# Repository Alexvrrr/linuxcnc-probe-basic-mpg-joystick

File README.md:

# Кастомный USB-пульт (MPG + аналоговый стик) для LinuxCNC 2.9.10 и Probe Basic

Готовый проект аппаратно-программного пульта ручного управления (Pendant / MPG) для станка с ЧПУ под управлением **LinuxCNC 2.9.10** (плата **Mesa 7i92**) и графического интерфейса **Probe Basic (QtPyVCP)**.

---

## 1. Возможности и архитектура

* **Контроллер пульта:** Arduino Leonardo / Pro Micro (ATmega32U4), работающий как стандартный USB HID-геймпад (`Joystick.h`).
* **Квадратурный MPG-энкодер:** Считывание фаз `A` и `B` по аппаратным прерываниям Arduino (`INT1` / `INT0`), буферизация и мгновенный сброс хвоста очереди при остановке вращения (исключает инерционный «доезд» осей).
* **Выбор активной оси (`X`, `Y`, `Z`):** Перемещение по шагам выполняется при удержании кнопки нужной оси и вращении энкодера (на время удержания аналоговый стик программно блокируется в центр).
* **Переключение шага (`Step`):** Циклический перебор `1.0` → `0.1` → `0.01` мм одной кнопкой с выводом текущего значения на LCD-индикатор в интерфейсе Probe Basic.
* **Непрерывные перемещения:**
  * 2-осевой аналоговый стик (`X`, `Y`) с мёртвой зоной и экспоненциальной кривой отклика (`joyhandle`).
  * Кнопки `Z+` и `Z-` для плавного перемещения по оси Z.
  * Регулировка скорости непрерывных перемещений штатным слайдером **Feed Override** в Probe Basic.
* **Работа в любых режимах:** Поддержка перемещений как до поиска домов (**Joint mode**, `joint.0..2`), так и после (**World mode**, `axis.x/y/z`).
* **Аварийный стоп:** Выделенная аппаратная кнопка `E-Stop`.

---

## 2. Схема распайки пинов Arduino (Leonardo / Pro Micro)

Все дискретные входы (кнопки и фазы энкодера) используют внутреннюю подтяжку к плюсу питания (`INPUT_PULLUP`) и замыкаются на общий провод (**GND**).

| Пин Arduino | Назначение в пульте | Тип сигнала / подключение | Кнопка / Ось в `Joystick.h` | Имя пина в LinuxCNC (`hal_input`) |
| :--- | :--- | :--- | :--- | :--- |
| **D2** (`INT1`) | Энкодер MPG — **Фаза A** | Аппаратное прерывание, замыкание на `GND` | Виртуальная кнопка `7` (`MPG+`) | `input.0.btn-tr` |
| **D3** (`INT0`) | Энкодер MPG — **Фаза B** | Аппаратное прерывание, замыкание на `GND` | Виртуальная кнопка `8` (`MPG-`) | `input.0.btn-tl2` |
| **D4** | Выбор оси **X** (`BTN_X`) | Кнопка без фиксации на `GND` | Кнопка `4` | `input.0.btn-y` |
| **D5** | Выбор оси **Y** (`BTN_Y`) | Кнопка без фиксации на `GND` | Кнопка `5` | `input.0.btn-z` |
| **D6** | Выбор оси **Z** (`BTN_Z`) | Кнопка без фиксации на `GND` | Кнопка `6` | `input.0.btn-tl` |
| **D7** | Непрерывный ход **Z+** (`BTN_ZP`) | Кнопка без фиксации на `GND` | Кнопка `2` | `input.0.btn-a` |
| **D8** | Аварийный стоп **E-Stop** (`BTN_ESTOP`) | Кнопка на `GND` | Кнопка `1` | `input.0.btn-b` |
| **D9** | Переключение шага **Step** (`BTN_STEP`) | Кнопка без фиксации на `GND` | Кнопка `0` | `input.0.btn-c` |
| **D14** (`MISO`) | Непрерывный ход **Z-** (`BTN_ZM`) | Кнопка без фиксации на `GND` | Кнопка `3` | `input.0.btn-x` |
| **A0** | Аналоговый стик — **Ось X** | Средний вывод потенциометра (`0..5V`) | Ось `X` (`0..1023`, инверсия в скетче) | `input.0.abs-x-position` |
| **A1** | Аналоговый стик — **Ось Y** | Средний вывод потенциометра (`0..5V`) | Ось `Y` (`0..1023`, инверсия в HAL) | `input.0.abs-y-position` |
| **VCC / 5V** | Питание периферии | Питание активного MPG и потенциометров стика | — | — |
| **GND** | Общий провод | Общая земля для всех кнопок, стика и MPG | — | — |

> **Примечания по электрической части:**
> * На плате **Arduino Pro Micro** пин `14` подписан как **`MISO`** (верхний правый угол платы).
> * При длине кабеля более 1.5–2 м используйте экранированный кабель (экран на `GND` со стороны Arduino) и керамические конденсаторы `0.1 мкФ` между `A0`/`A1` и `GND`.

---

## 3. Прошивка Arduino (`MPG_Joystick.ino`)

Для компиляции требуется библиотека [ArduinoJoystickLibrary](https://github.com/MHeironimus/ArduinoJoystickLibrary).

```cpp
#include <Joystick.h>

Joystick_ Joystick(
  JOYSTICK_DEFAULT_REPORT_ID,
  JOYSTICK_TYPE_GAMEPAD,
  9, 0,                  // 9 кнопок (индексы 0..8), 0 хатов
  true, true, false,     // Оси X и Y включены, Z выключена
  false, false, false,
  false, false, false,
  false, false
);

// --- Пины подключения ---
const int PIN_ENC_A  = 2;  // Фаза A энкодера (аппаратное прерывание INT1)
const int PIN_ENC_B  = 3;  // Фаза B энкодера (аппаратное прерывание INT0)
const int BTN_X      = 4;  // Выбор оси X
const int BTN_Y      = 5;  // Выбор оси Y
const int BTN_Z      = 6;  // Выбор оси Z
const int BTN_ZP     = 7;  // Непрерывное движение Z+
const int BTN_ZM     = 14; // Непрерывное движение Z-
const int BTN_STEP   = 9;  // Переключение шага (1 -> 0.1 -> 0.01)
const int BTN_ESTOP  = 8;  // Аварийный стоп (E-Stop)
const int ADC_X      = A0; // Аналоговый стик X
const int ADC_Y      = A1; // Аналоговый стик Y

// --- Виртуальные кнопки джойстика для импульсов MPG ---
const int BTN_MPG_PLUS  = 7; // В LinuxCNC: input.0.btn-tr (вращение +)
const int BTN_MPG_MINUS = 8; // В LinuxCNC: input.0.btn-tl2 (вращение -)

// --- Переменные квадратурного энкодера ---
volatile long encTicks = 0;
volatile uint8_t prevAB = 0;

const int8_t QUAD_TABLE[16] = {
   0, -1,  1,  0,
   1,  0,  0, -1,
  -1,  0,  0,  1,
   0,  1, -1,  0
};

const int TICKS_PER_DETENT = 4;

// --- Переменные формирования импульсов и мгновенной остановки ---
long sentDetents = 0;
long prevTicks = 0;
unsigned long lastTickTime = 0;
unsigned long pulseTimer = 0;

int pulseState = 0;
int activeMpgBtn = -1;

const unsigned long PULSE_MS = 2;         // 2 мс импульс + 2 мс пауза (до 250 щелчков/сек)
const unsigned long STOP_TIMEOUT_MS = 25; // Сброс хвоста очереди через 25 мс после остановки руки

// --- Антидребезг кнопок выбора оси ---
bool btnAxisState[3] = {false, false, false};
bool btnAxisLastRaw[3] = {false, false, false};
unsigned long btnAxisTimer[3] = {0, 0, 0};
const unsigned long DEBOUNCE_MS = 20;

void isrEncoder() {
  uint8_t curAB = (digitalRead(PIN_ENC_A) << 1) | digitalRead(PIN_ENC_B);
  uint8_t idx = (prevAB << 2) | curAB;
  encTicks += QUAD_TABLE[idx];
  prevAB = curAB;
}

bool readDebounced(int pin, int idx) {
  bool raw = !digitalRead(pin);
  if (raw != btnAxisLastRaw[idx]) {
    btnAxisTimer[idx] = millis();
    btnAxisLastRaw[idx] = raw;
  }
  if ((millis() - btnAxisTimer[idx]) >= DEBOUNCE_MS) {
    btnAxisState[idx] = raw;
  }
  return btnAxisState[idx];
}

void setup() {
  pinMode(BTN_X,     INPUT_PULLUP);
  pinMode(BTN_Y,     INPUT_PULLUP);
  pinMode(BTN_Z,     INPUT_PULLUP);
  pinMode(BTN_ZP,    INPUT_PULLUP);
  pinMode(BTN_ZM,    INPUT_PULLUP);
  pinMode(BTN_STEP,  INPUT_PULLUP);
  pinMode(BTN_ESTOP, INPUT_PULLUP);

  pinMode(PIN_ENC_A, INPUT_PULLUP);
  pinMode(PIN_ENC_B, INPUT_PULLUP);

  prevAB = (digitalRead(PIN_ENC_A) << 1) | digitalRead(PIN_ENC_B);
  attachInterrupt(digitalPinToInterrupt(PIN_ENC_A), isrEncoder, CHANGE);
  attachInterrupt(digitalPinToInterrupt(PIN_ENC_B), isrEncoder, CHANGE);

  Joystick.begin();
  Joystick.setXAxisRange(0, 1023);
  Joystick.setYAxisRange(0, 1023);
  Joystick.setXAxis(512);
  Joystick.setYAxis(512);
}

void loop() {
  unsigned long now = millis();

  bool btnX = readDebounced(BTN_X, 0);
  bool btnY = readDebounced(BTN_Y, 1);
  bool btnZ = readDebounced(BTN_Z, 2);

  if (btnX || btnY || btnZ) {
    Joystick.setXAxis(512);
    Joystick.setYAxis(512);
  } else {
    Joystick.setXAxis(1023 - analogRead(ADC_X));
    Joystick.setYAxis(analogRead(ADC_Y));
  }

  noInterrupts();
  long currentTicks = encTicks;
  interrupts();

  if (currentTicks != prevTicks) {
    lastTickTime = now;
    prevTicks = currentTicks;
  }

  long targetDetents = currentTicks / TICKS_PER_DETENT;

  if (pulseState == 0 && (now - lastTickTime > STOP_TIMEOUT_MS)) {
    sentDetents = targetDetents;
  }

  if (pulseState == 0) {
    if (targetDetents > sentDetents) {
      activeMpgBtn = BTN_MPG_PLUS;
      Joystick.setButton(activeMpgBtn, 1);
      sentDetents++;
      pulseTimer = now;
      pulseState = 1;
    } else if (targetDetents < sentDetents) {
      activeMpgBtn = BTN_MPG_MINUS;
      Joystick.setButton(activeMpgBtn, 1);
      sentDetents--;
      pulseTimer = now;
      pulseState = 1;
    }
  } else if (pulseState == 1) {
    if (now - pulseTimer >= PULSE_MS) {
      Joystick.setButton(activeMpgBtn, 0);
      pulseTimer = now;
      pulseState = 2;
    }
  } else if (pulseState == 2) {
    if (now - pulseTimer >= PULSE_MS) {
      pulseState = 0;
    }
  }

  Joystick.setButton(0, !digitalRead(BTN_STEP));
  Joystick.setButton(1, !digitalRead(BTN_ESTOP));
  Joystick.setButton(2, !digitalRead(BTN_ZP));
  Joystick.setButton(3, !digitalRead(BTN_ZM));
  Joystick.setButton(4, btnX);
  Joystick.setButton(5, btnY);
  Joystick.setButton(6, btnZ);

  delay(1);
}
```

---

## 4. Конфигурация LinuxCNC 2.9.10

### 4.1. Настройка прав доступа USB (`udev`)
Создайте правило `/etc/udev/rules.d/99-joystick.rules` (подставив ваши `idVendor` и `idProduct` из `cat /proc/bus/input/devices`):
```text
SUBSYSTEM=="input", ATTRS{idVendor}=="XXXX", ATTRS{idProduct}=="YYYY", MODE="0666"
```
Примените правила:
```bash
sudo udevadm control --reload-rules && sudo udevadm trigger
```

### 4.2. Компонент переключения шага (`mpg_joy.py`)
Поместите в папку конфигурации станка и сделайте исполняемым (`chmod +x mpg_joy.py`):

```python
#!/usr/bin/env python3
import hal
import time

h = hal.component("mpg_joy")

h.newpin("btn-step", hal.HAL_BIT, hal.HAL_IN)
h.newpin("step-out", hal.HAL_FLOAT, hal.HAL_OUT)
h.newpin("led-1", hal.HAL_BIT, hal.HAL_OUT)
h.newpin("led-01", hal.HAL_BIT, hal.HAL_OUT)
h.newpin("led-001", hal.HAL_BIT, hal.HAL_OUT)

h.ready()

steps = [1.0, 0.1, 0.01]
step_idx = 0
prev_step = False

try:
    while True:
        cur_step = h["btn-step"]
        if cur_step and not prev_step:
            step_idx = (step_idx + 1) % 3
        prev_step = cur_step

        h["step-out"] = steps[step_idx]
        h["led-1"] = (step_idx == 0)
        h["led-01"] = (step_idx == 1)
        h["led-001"] = (step_idx == 2)

        time.sleep(0.01)
except KeyboardInterrupt:
    raise SystemExit
```

### 4.3. Логика пульта (`MPG_Alex.hal`)

```hal
# 1. Загрузка драйвера джойстика и Python-компонента переключения шага
loadusr -W hal_input -KRAL Arduino
loadusr -W ./mpg_joy.py

# 2. Загрузка RT-компонентов (счётчик MPG, сглаживание стика и масштаб скорости)
loadrt updown names=mpg_rt_cnt
loadrt joyhandle count=2
loadrt scale names=joy_speed_scale

addf mpg_rt_cnt servo-thread
addf joyhandle.0 servo-thread
addf joyhandle.1 servo-thread
addf joy_speed_scale servo-thread

# 3. Настройка сглаживания аналогового стика X/Y (с инверсией оси Y)
setp joyhandle.0.deadband 0.1
setp joyhandle.0.power 2.0
setp joyhandle.0.scale 1.0

setp joyhandle.1.deadband 0.1
setp joyhandle.1.power 2.0
setp joyhandle.1.scale -1.0

# 4. Переключение шага (1 -> 0.1 -> 0.01) кнопкой Step
net btn-step mpg_joy.btn-step <= input.0.btn-c

# 5. Настройка MPG-энкодера (работает и до Homed, и после Homed; режим мгновенной остановки 1)
setp axis.x.jog-vel-mode 1
setp axis.y.jog-vel-mode 1
setp axis.z.jog-vel-mode 1
setp joint.0.jog-vel-mode 1
setp joint.1.jog-vel-mode 1
setp joint.2.jog-vel-mode 1

net mpg-a mpg_rt_cnt.countup   <= input.0.btn-tr
net mpg-b mpg_rt_cnt.countdown <= input.0.btn-tl2

net mpg-scale  mpg_joy.step-out => axis.x.jog-scale axis.y.jog-scale axis.z.jog-scale joint.0.jog-scale joint.1.jog-scale joint.2.jog-scale
net mpg-counts mpg_rt_cnt.count => axis.x.jog-counts axis.y.jog-counts axis.z.jog-counts joint.0.jog-counts joint.1.jog-counts joint.2.jog-counts

net btn-xsig axis.x.jog-enable joint.0.jog-enable <= input.0.btn-y
net btn-ysig axis.y.jog-enable joint.1.jog-enable <= input.0.btn-z
net btn-zsel axis.z.jog-enable joint.2.jog-enable <= input.0.btn-tl

# 6. Управление скоростью джойстика со слайдера Feed Override Probe Basic
setp joy_speed_scale.gain 3000.0
net feed-override-val joy_speed_scale.in <= halui.feed-override.value
net jog-speed <= joy_speed_scale.out
net jog-speed => halui.joint.jog-speed

# 7. Непрерывные перемещения (стик X/Y и кнопки Z+/Z-)
unlinkp halui.axis.x.analog
unlinkp halui.axis.y.analog
unlinkp halui.joint.0.analog
unlinkp halui.joint.1.analog
unlinkp halui.axis.z.plus
unlinkp halui.axis.z.minus
unlinkp halui.joint.2.plus
unlinkp halui.joint.2.minus

net joy-x-raw joyhandle.0.in <= input.0.abs-x-position
net joy-y-raw joyhandle.1.in <= input.0.abs-y-position
net joy-x     halui.axis.x.analog halui.joint.0.analog <= joyhandle.0.out
net joy-y     halui.axis.y.analog halui.joint.1.analog <= joyhandle.1.out

net btn-zplus  halui.axis.z.plus  halui.joint.2.plus  <= input.0.btn-a
net btn-zminus halui.axis.z.minus halui.joint.2.minus <= input.0.btn-x

# 8. Кнопка E-Stop (аварийный стоп)
unlinkp halui.estop.activate
net btn-estop halui.estop.activate <= input.0.btn-b
```

### 4.4. Настройки `.ini` и индикация в Probe Basic (`probe_basic_postgui.hal`)

В `.ini` файле станка:
```ini
[EMCMOT]
SERVO_PERIOD = 1000000

[HAL]
HALUI = halui
TWOPASS = on
HALFILE = основной_файл.hal
HALFILE = custom.hal
HALFILE = MPG_Alex.hal
POSTGUI_HALFILE = probe_basic_postgui.hal
```

В сайдбар интерфейса Probe Basic (через `editvcp`) добавлен виджет `HalLCDNumber` (`qtpyvcp.widgets.hal_widgets.hal_lcd`) с `objectName = lcd_mpg_step`, `digitCount = 4`, `smallDecimalPoint = True`, `segmentStyle = Flat`.

Подключение в конце `probe_basic_postgui.hal`:
```hal
# Вывод выбранного шага MPG в LCD-индикатор сайдбара
net mpg-scale => qtpyvcp.lcd-mpg-step.float-value
```

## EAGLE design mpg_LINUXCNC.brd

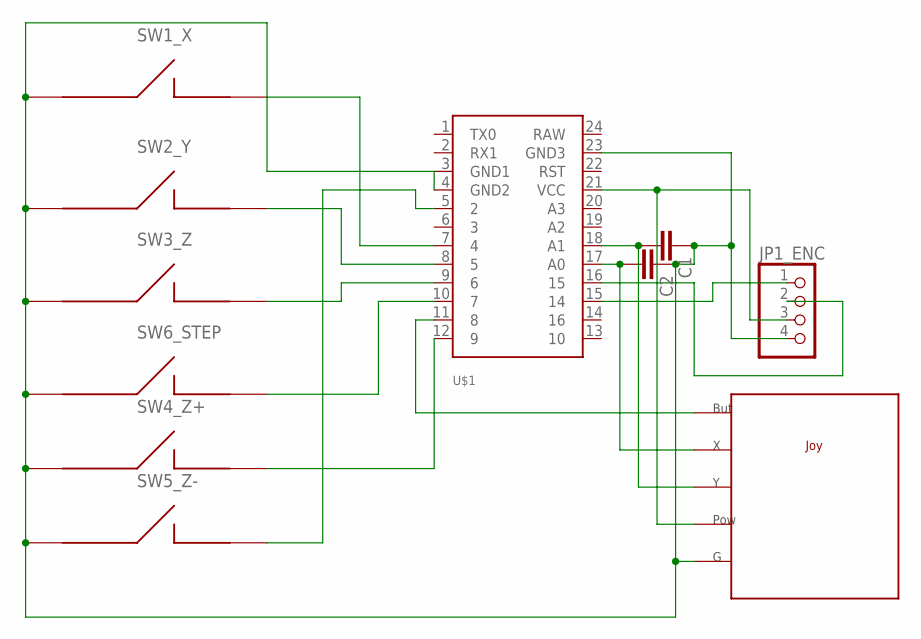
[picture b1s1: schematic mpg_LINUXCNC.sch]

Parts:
C1, C2: C-EUC0805; C0805
JOY1: JOY
JP1_ENC: PINHD-1X4; 1X04
SW1_X, SW2_Y, SW3_Z: B2
SW4_Z+, SW5_Z-, SW6_STEP: B1
U$1: ARDUINOPROMICRO1; PROMICRO

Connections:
GND: C1.1, C2.1, JOY1.P$5, JP1_ENC.4, SW1_X.P$1, SW1_X.P$3, SW2_Y.P$1, SW2_Y.P$3, SW3_Z.P$1, SW3_Z.P$3, SW4_Z+.P$1, SW4_Z+.P$3, SW5_Z-.P$1, SW5_Z-.P$3, SW6_STEP.P$1, SW6_STEP.P$3, U$1.3 (GND1), U$1.4 (GND2), U$1.23 (GND3)
unnamed: SW1_X.P$2, SW1_X.P$4, U$1.7 (4)
unnamed: SW2_Y.P$2, SW2_Y.P$4, U$1.8 (5)
unnamed: SW3_Z.P$2, SW3_Z.P$4, U$1.9 (6)
unnamed: SW6_STEP.P$2, SW6_STEP.P$4, U$1.10 (7)
unnamed: SW5_Z-.P$2, SW5_Z-.P$4, U$1.5 (2)
unnamed: JOY1.P$1, U$1.11 (8)
unnamed: C2.2, JOY1.P$2, U$1.17 (A0)
unnamed: C1.2, JOY1.P$3, U$1.18 (A1)
unnamed: JOY1.P$4, JP1_ENC.3, U$1.21 (VCC)
unnamed: SW4_Z+.P$2, SW4_Z+.P$4, U$1.12 (9)
unnamed: JP1_ENC.1, U$1.15 (14)
unnamed: JP1_ENC.2, U$1.16 (15)

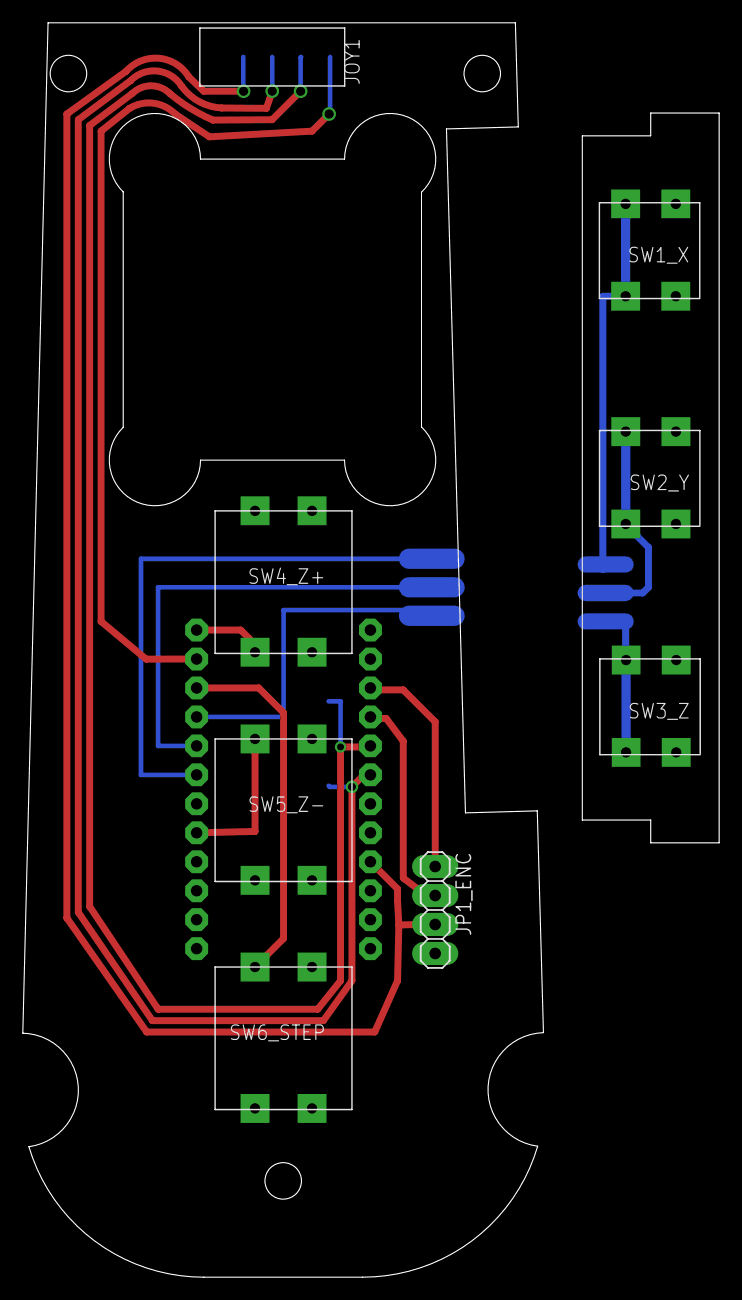
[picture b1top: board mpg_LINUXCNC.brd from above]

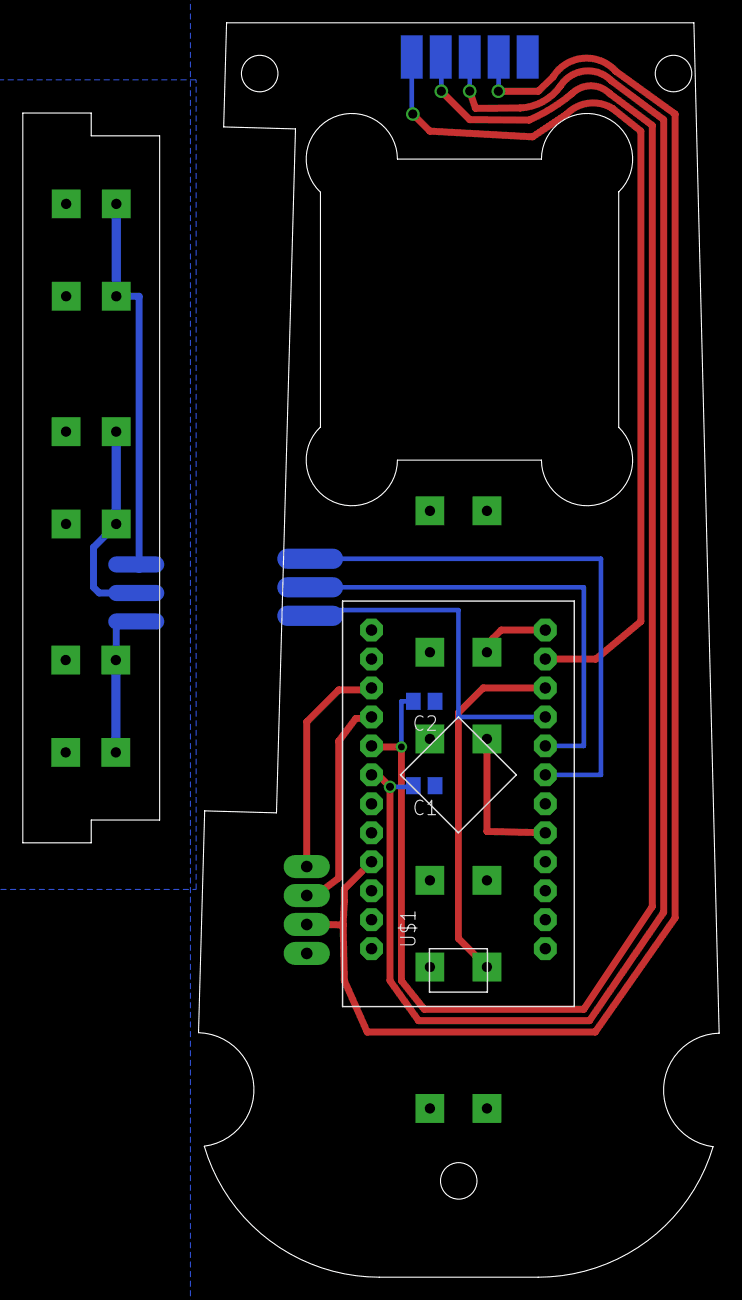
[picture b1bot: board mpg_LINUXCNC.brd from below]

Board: 2 copper layers, 61.1 x 110.0 mm, 11 parts (3 on the bottom side), 13 nets.
